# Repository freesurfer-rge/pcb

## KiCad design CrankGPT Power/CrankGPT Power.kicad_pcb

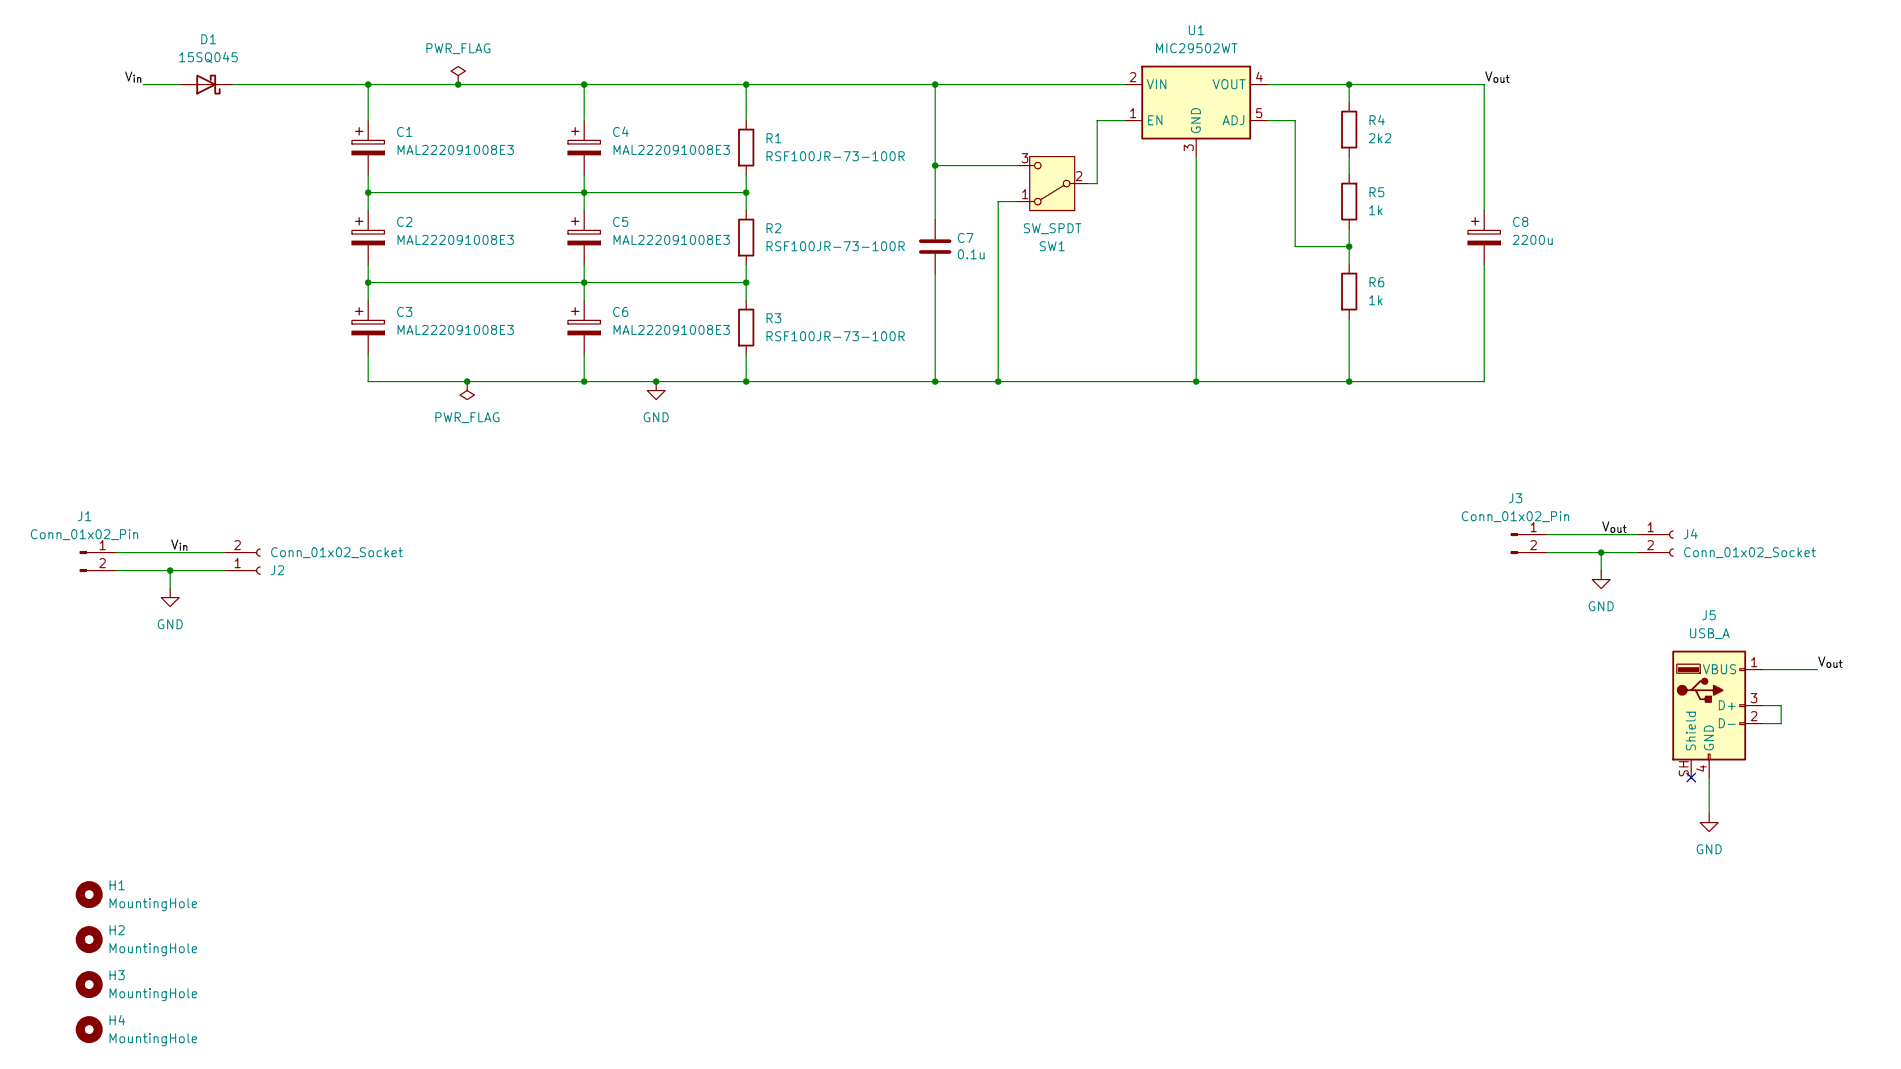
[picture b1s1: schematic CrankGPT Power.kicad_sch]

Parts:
C1, C2, C3, C4, C5, C6: MAL222091008E3; CP_Radial_D18.0mm_P7.50mm
C7: 0.1u; C_Disc_D4.3mm_W1.9mm_P5.00mm
C8: 2200u; CP_Radial_D10.0mm_P5.00mm
D1: 15SQ045; D_P600_R-6_P20.00mm_Horizontal
H1, H2, H3, H4: MountingHole; MountingHole_2.7mm_M2.5
J1, J3: Conn_01x02_Pin; PinHeader_1x02_P2.54mm_Vertical
J2, J4: Conn_01x02_Socket; JST_NV_B02P-NV_1x02_P5.00mm_Vertical
J5: USB_A; USB_A_Molex_67643_Horizontal
R1, R2, R3: RSF100JR-73-100R; R_Axial_DIN0414_L11.9mm_D4.5mm_P15.24mm_Horizontal
R4: 2k2; R_Axial_DIN0207_L6.3mm_D2.5mm_P7.62mm_Horizontal
R5, R6: 1k; R_Axial_DIN0207_L6.3mm_D2.5mm_P7.62mm_Horizontal
SW1: SW_SPDT; SW_Slide_SPDT_Angled_CK_OS102011MA1Q
U1: MIC29502WT; TO-220-5_P3.4x3.7mm_StaggerEven_Lead3.8mm_Vertical

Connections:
/V_{in}: D1.2 (A), J1.1, J2.2
/V_{out}: C8.1, J3.1, J4.1, J5.1 (VBUS), R4.1, U1.4 (VOUT)
GND: C3.2, C6.2, C7.1, C8.2, J1.2, J2.1, J3.2, J4.2, J5.4 (GND), R3.2, R6.2, SW1.1 (A), U1.3 (GND)
unnamed: C1.2, C2.1, C4.2, C5.1, R1.2, R2.1
unnamed: C2.2, C3.1, C5.2, C6.1, R2.2, R3.1
unnamed: C1.1, C4.1, C7.2, D1.1 (K), R1.1, SW1.3 (C), U1.2 (VIN)
unnamed: J5.2 (D-), J5.3 (D+)
unnamed: R4.2, R5.2
unnamed: SW1.2 (B), U1.1 (EN)
unnamed: R5.1, R6.1, U1.5 (ADJ)

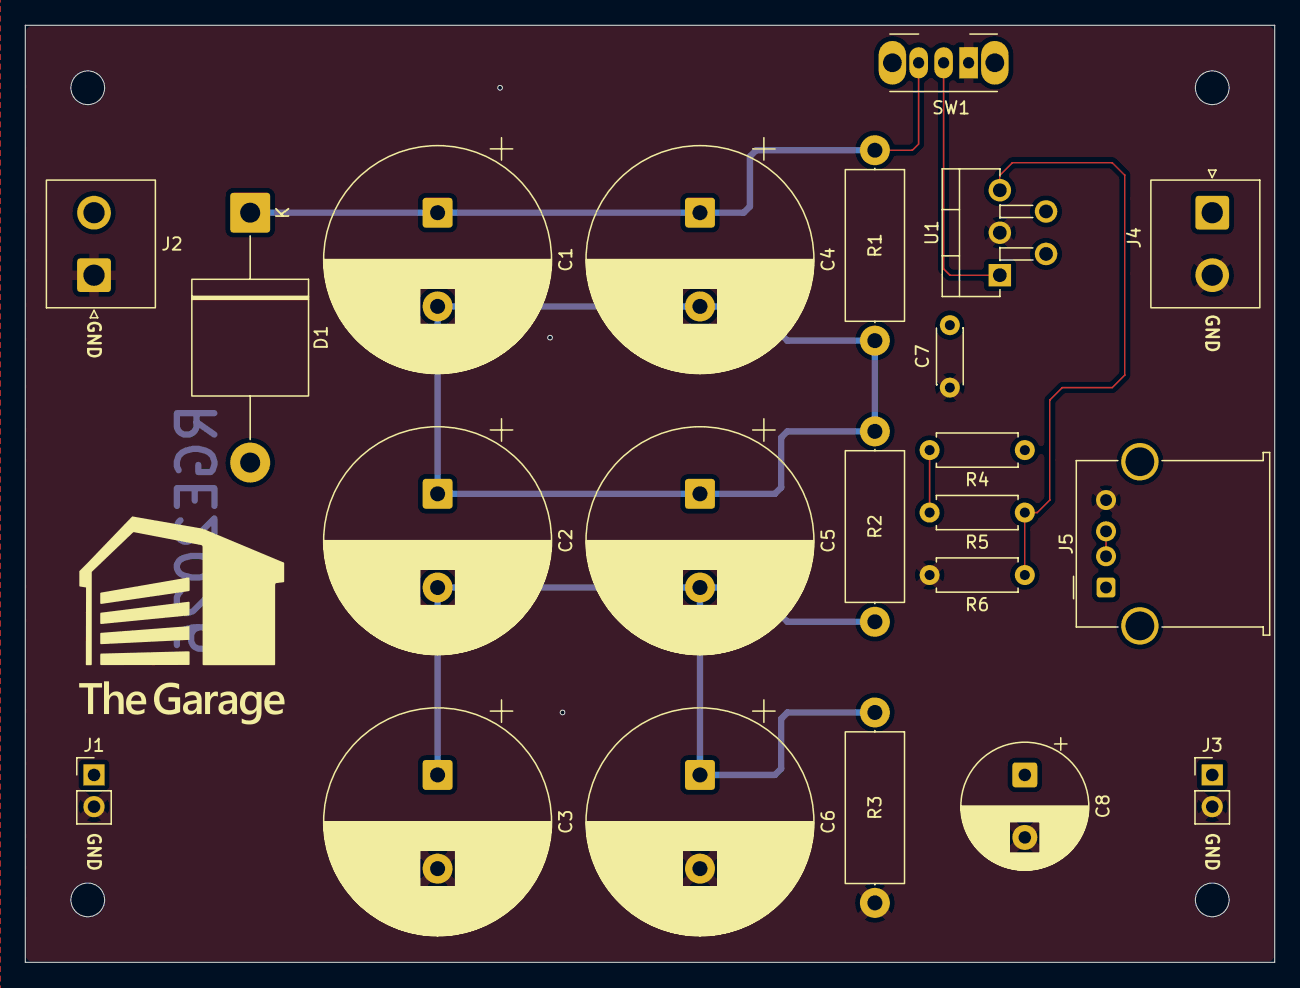
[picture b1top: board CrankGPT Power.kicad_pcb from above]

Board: 2 copper layers, 100.0 x 75.0 mm, 26 parts (0 on the bottom side), 10 nets.

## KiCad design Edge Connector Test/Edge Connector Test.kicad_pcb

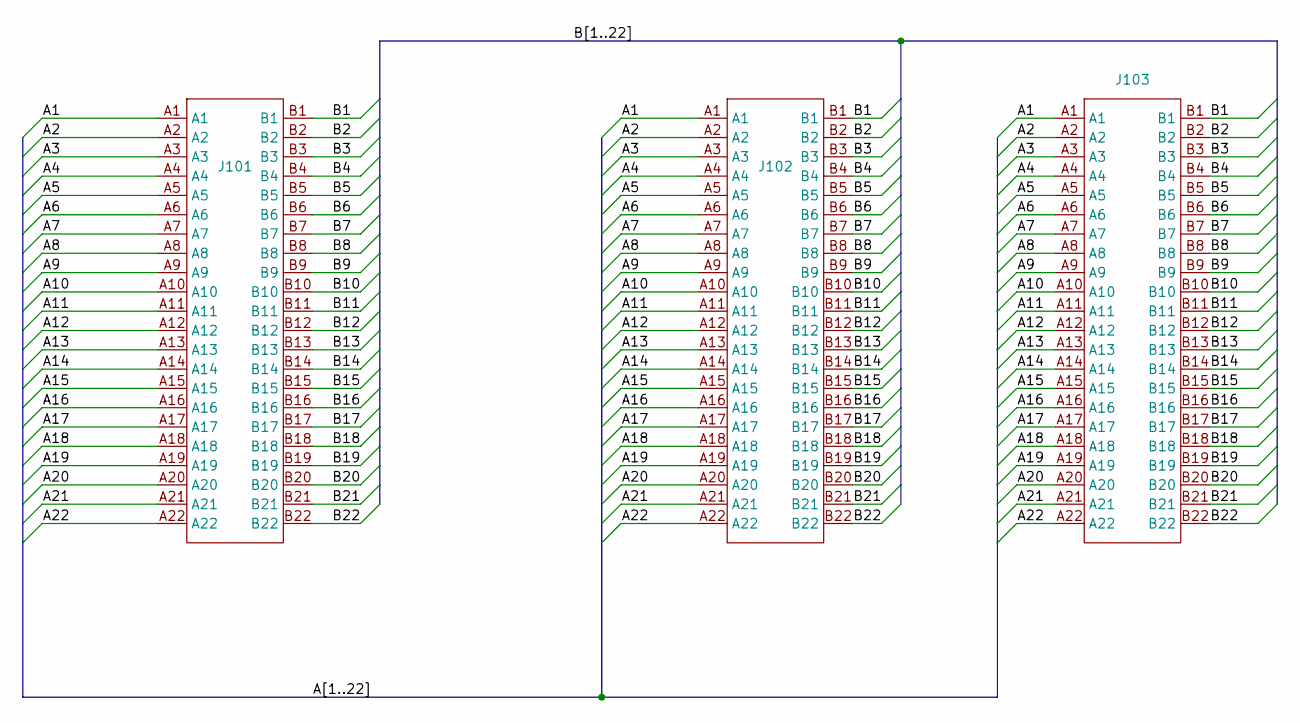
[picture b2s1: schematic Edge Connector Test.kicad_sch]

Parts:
J101, J102: TE-5530843-4-Mount
J103: TE-5530843-4-Edge

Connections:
/A1: J101.A1, J102.A1, J103.A1
/A2: J101.A2, J102.A2, J103.A2
/A3: J101.A3, J102.A3, J103.A3
/A4: J101.A4, J102.A4, J103.A4
/A5: J101.A5, J102.A5, J103.A5
/A6: J101.A6, J102.A6, J103.A6
/A7: J101.A7, J102.A7, J103.A7
/A8: J101.A8, J102.A8, J103.A8
/A9: J101.A9, J102.A9, J103.A9
/A10: J101.A10, J102.A10, J103.A10
/A11: J101.A11, J102.A11, J103.A11
/A12: J101.A12, J102.A12, J103.A12
/A13: J101.A13, J102.A13, J103.A13
/A14: J101.A14, J102.A14, J103.A14
/A15: J101.A15, J102.A15, J103.A15
/A16: J101.A16, J102.A16, J103.A16
/A17: J101.A17, J102.A17, J103.A17
/A18: J101.A18, J102.A18, J103.A18
/A19: J101.A19, J102.A19, J103.A19
/A20: J101.A20, J102.A20, J103.A20
/A21: J101.A21, J102.A21, J103.A21
/A22: J101.A22, J102.A22, J103.A22
/B1: J101.B1, J102.B1, J103.B1
/B2: J101.B2, J102.B2, J103.B2
/B3: J101.B3, J102.B3, J103.B3
/B4: J101.B4, J102.B4, J103.B4
/B5: J101.B5, J102.B5, J103.B5
/B6: J101.B6, J102.B6, J103.B6
/B7: J101.B7, J102.B7, J103.B7
/B8: J101.B8, J102.B8, J103.B8
/B9: J101.B9, J102.B9, J103.B9
/B10: J101.B10, J102.B10, J103.B10
/B11: J101.B11, J102.B11, J103.B11
/B12: J101.B12, J102.B12, J103.B12
/B13: J101.B13, J102.B13, J103.B13
/B14: J101.B14, J102.B14, J103.B14
/B15: J101.B15, J102.B15, J103.B15
/B16: J101.B16, J102.B16, J103.B16
/B17: J101.B17, J102.B17, J103.B17
/B18: J101.B18, J102.B18, J103.B18
/B19: J101.B19, J102.B19, J103.B19
/B20: J101.B20, J102.B20, J103.B20
/B21: J101.B21, J102.B21, J103.B21
/B22: J101.B22, J102.B22, J103.B22

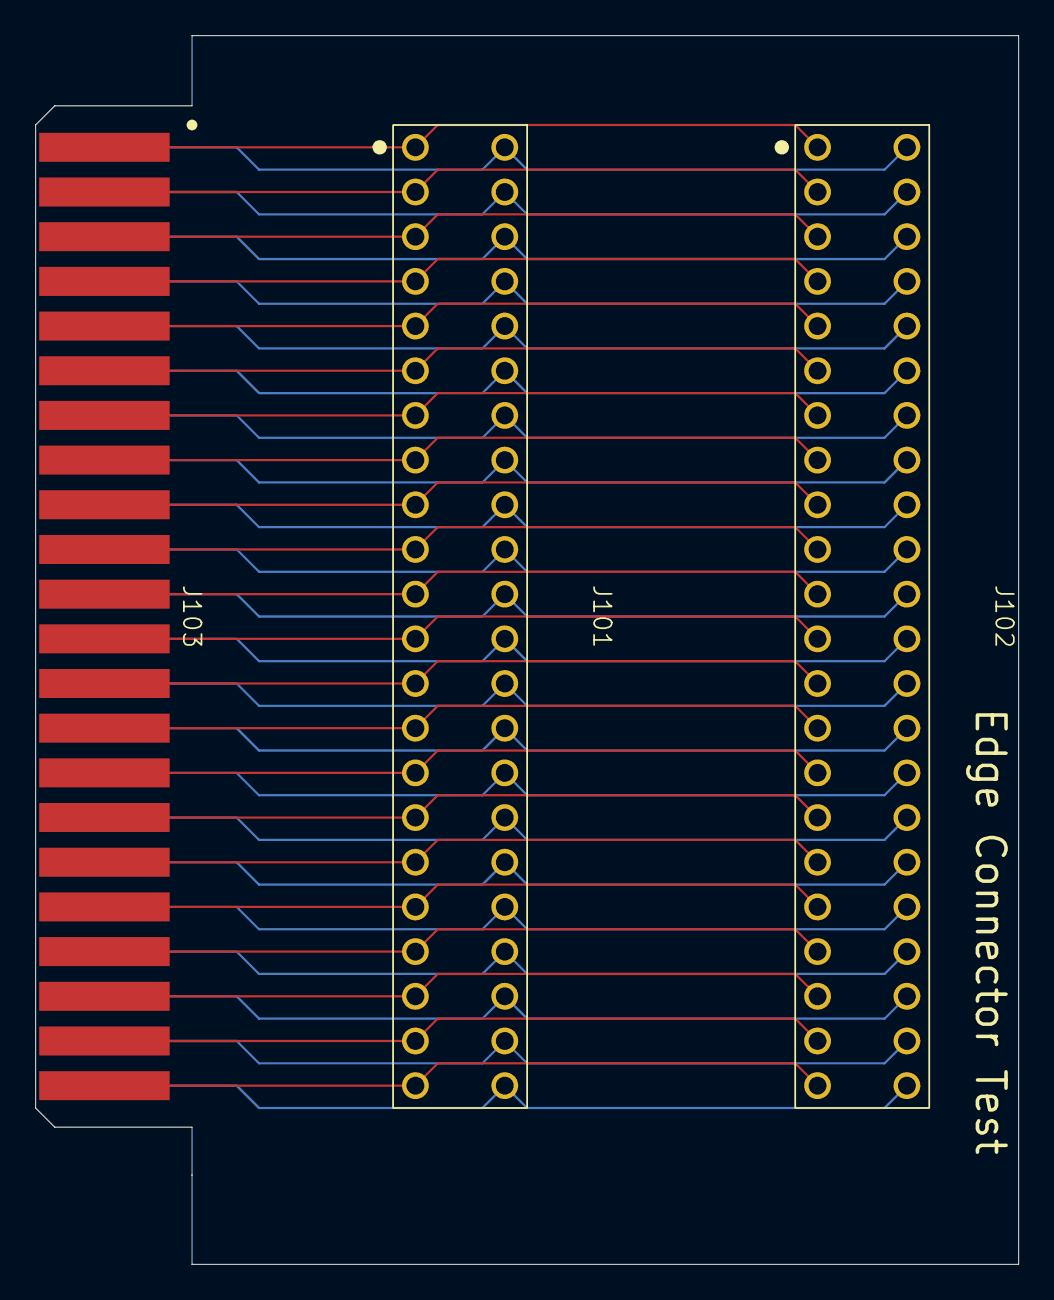
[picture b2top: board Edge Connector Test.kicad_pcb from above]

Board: 2 copper layers, 55.9 x 69.8 mm, 3 parts (0 on the bottom side), 44 nets.

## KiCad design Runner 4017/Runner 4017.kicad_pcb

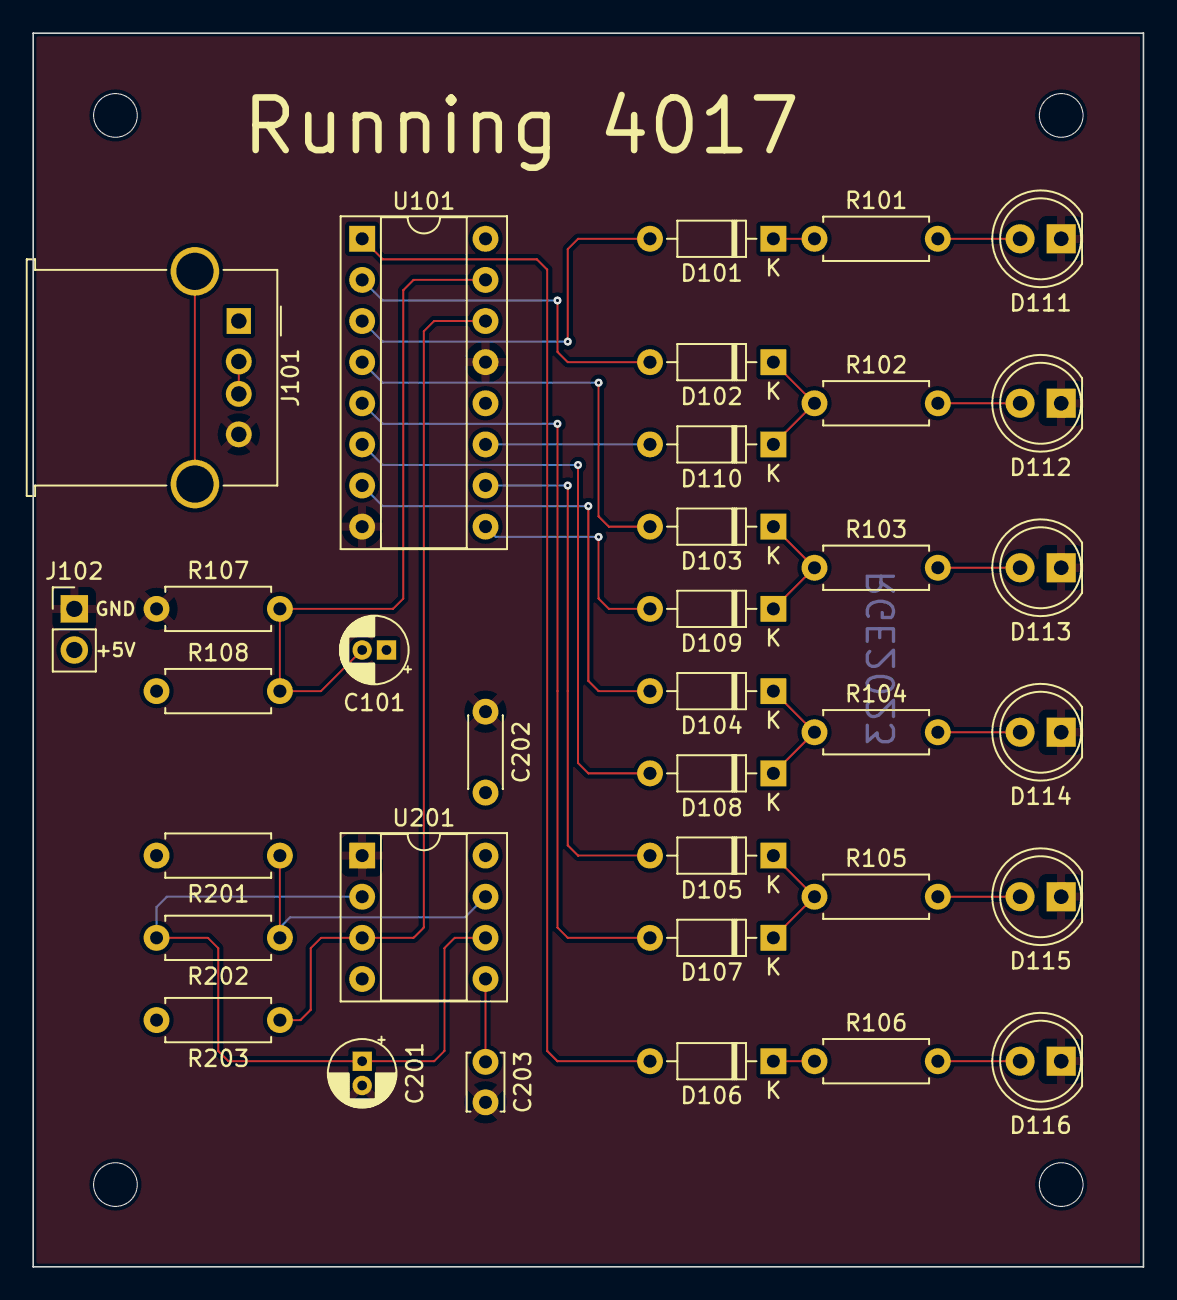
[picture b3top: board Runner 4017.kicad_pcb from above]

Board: 2 copper layers, 68.6 x 76.2 mm, 39 parts (0 on the bottom side), 30 nets.

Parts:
C101, C201: 10u; CP_Radial_D4.0mm_P1.50mm
C202: 0.1u; C_Disc_D4.3mm_W1.9mm_P5.00mm
C203: 0.01u; C_Disc_D3.4mm_W2.1mm_P2.50mm
D101, D102, D103, D104, D105, D106, D107, D108, D109, D110: 1N4148; D_DO-35_SOD27_P7.62mm_Horizontal
D111, D112, D113, D114, D115, D116: LED; LED_D5.0mm
H101, H102, H103, H104: MountingHole; MountingHole_2.7mm_M2.5_ISO7380
J101: USB_A; USB_A_Molex_67643_Horizontal
J102: Conn_01x02_Pin; PinHeader_1x02_P2.54mm_Vertical
R101, R102, R103, R104, R105, R106: R; R_Axial_DIN0207_L6.3mm_D2.5mm_P7.62mm_Horizontal
R107, R203: 1k; R_Axial_DIN0207_L6.3mm_D2.5mm_P7.62mm_Horizontal
R108: 100k; R_Axial_DIN0207_L6.3mm_D2.5mm_P7.62mm_Horizontal
R201: 10k; R_Axial_DIN0207_L6.3mm_D2.5mm_P7.62mm_Horizontal
R202: 22k; R_Axial_DIN0207_L6.3mm_D2.5mm_P7.62mm_Horizontal
U101: 4017; DIP-16_W7.62mm_Socket
U201: LM555xN; DIP-8_W7.62mm_Socket

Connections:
+5V: C101.1, C202.2, J101.1 (VBUS), J102.2, R108.1, R201.2, R203.2, U101.16 (VDD), U201.4 (R), U201.8 (VCC)
/Clock/CLK: R203.1, U101.14 (CLK), U201.3 (Q)
/Clock/DIVIDER: R201.1, R202.1, U201.7 (DIS)
/Clock/TRTHR: C201.1, R202.2, U201.2 (TR), U201.6 (THR)
/LED1: D101.1 (K), R101.1
/LED2: D102.1 (K), D110.1 (K), R102.1
/LED3: D103.1 (K), D109.1 (K), R103.1
/LED4: D104.1 (K), D108.1 (K), R104.1
/LED5: D105.1 (K), D107.1 (K), R105.1
/LED6: D106.1 (K), R106.1
/RESET: C101.2, R107.2, R108.2, U101.15 (Reset)
GND: C201.2, C202.1, C203.2, D111.1 (K), D112.1 (K), D113.1 (K), D114.1 (K), D115.1 (K), D116.1 (K), J101.4 (GND), J102.1, R107.1, U101.8 (VSS), U101.13 (CKEN), U201.1 (GND)
unnamed: D101.2 (A), U101.3 (Q0)
unnamed: D102.2 (A), U101.2 (Q1)
unnamed: D103.2 (A), U101.4 (Q2)
unnamed: D104.2 (A), U101.7 (Q3)
unnamed: D105.2 (A), U101.10 (Q4)
unnamed: D106.2 (A), U101.1 (Q5)
unnamed: D107.2 (A), U101.5 (Q6)
unnamed: D108.2 (A), U101.6 (Q7)
unnamed: D109.2 (A), U101.9 (Q8)
unnamed: D110.2 (A), U101.11 (Q9)
unnamed: D111.2 (A), R101.2
unnamed: D112.2 (A), R102.2
unnamed: D113.2 (A), R103.2
unnamed: D114.2 (A), R104.2
unnamed: D115.2 (A), R105.2
unnamed: D116.2 (A), R106.2
unnamed: J101.2 (D-), J101.3 (D+)
unnamed: C203.1, U201.5 (CV)

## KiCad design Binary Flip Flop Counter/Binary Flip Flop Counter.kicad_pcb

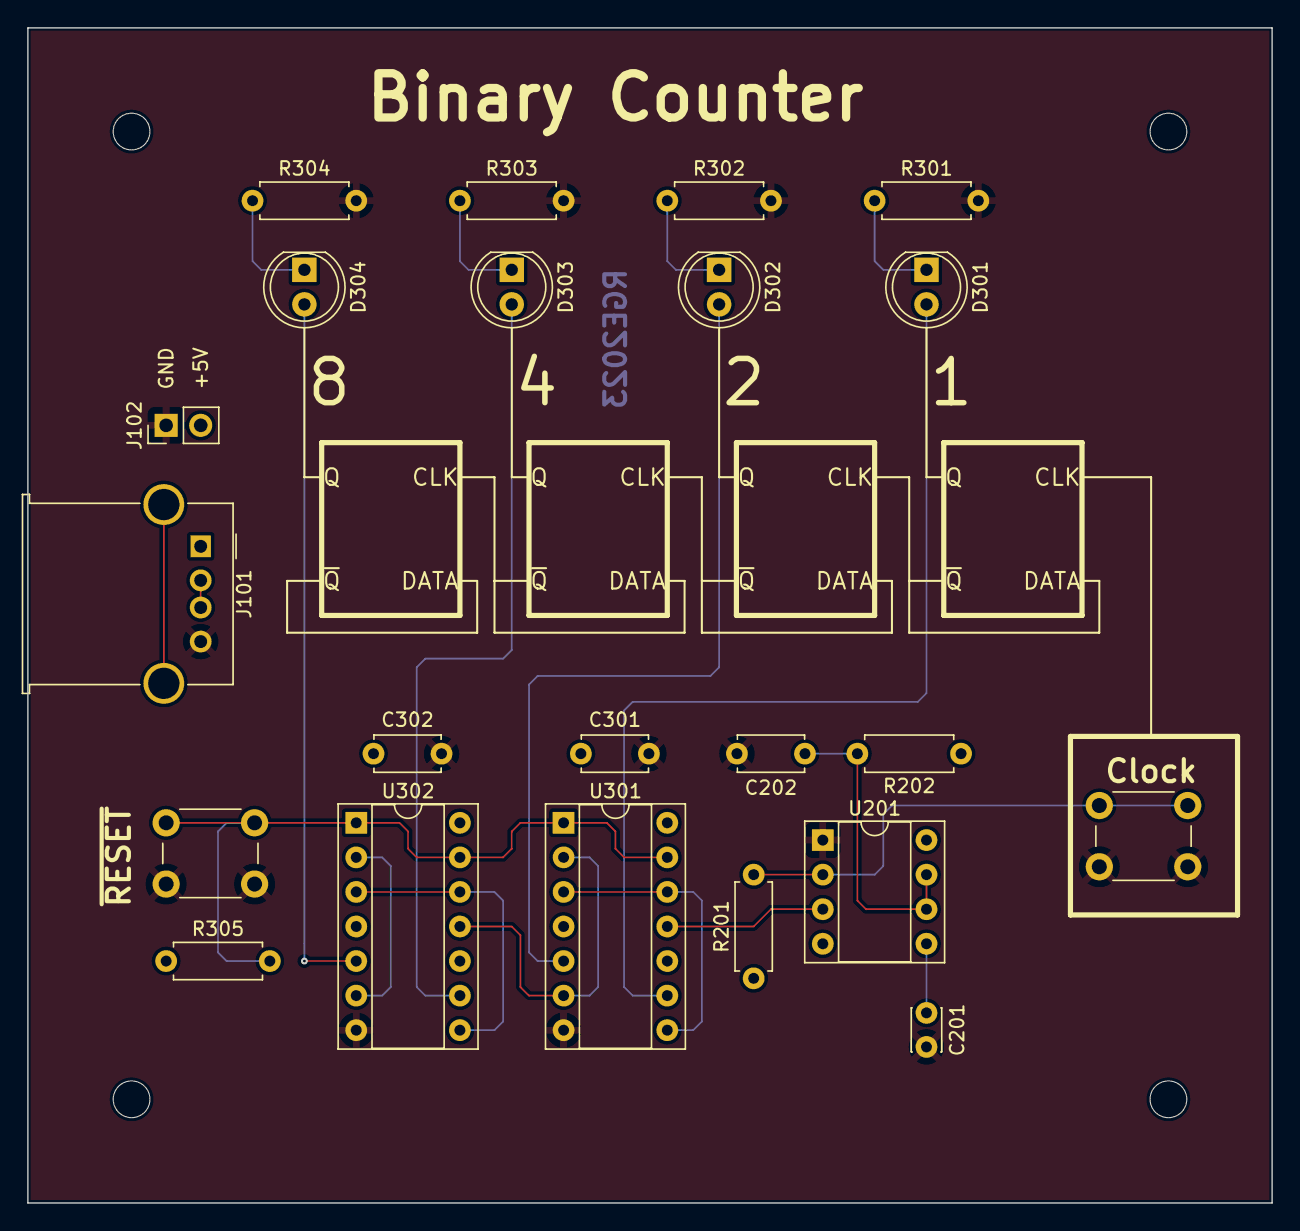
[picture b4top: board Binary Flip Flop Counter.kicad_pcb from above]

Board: 2 copper layers, 91.4 x 86.4 mm, 26 parts (0 on the bottom side), 20 nets.

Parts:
C201: 10nF; C_Disc_D3.0mm_W2.0mm_P2.50mm
C202, C301, C302: 0.1u; C_Disc_D4.7mm_W2.5mm_P5.00mm
D301, D302, D303, D304: LED; LED_D5.0mm
H101, H102, H103, H104: MountingHole; MountingHole_2.7mm_M2.5_ISO7380
J101: USB_A; USB_A_Molex_67643_Horizontal
J102: Conn_01x02_Pin; PinHeader_1x02_P2.54mm_Vertical
R201: 22k; R_Axial_DIN0207_L6.3mm_D2.5mm_P7.62mm_Horizontal
R202: 1M; R_Axial_DIN0207_L6.3mm_D2.5mm_P7.62mm_Horizontal
R301, R302, R303, R304: 4k7; R_Axial_DIN0207_L6.3mm_D2.5mm_P7.62mm_Horizontal
R305: 100k; R_Axial_DIN0207_L6.3mm_D2.5mm_P7.62mm_Horizontal
SW201, SW301: SW_Push; SW_PUSH_6mm_H4.3mm
U201: LM555xM; DIP-8_W7.62mm_Socket
U301, U302: 74HC74; DIP-14_W7.62mm_Socket

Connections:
+5V: C301.1, C302.1, J101.1 (VBUS), J102.2, R201.1, R202.1, R305.1, U201.4 (R), U201.8 (VCC), U301.4 (~S), U301.10 (~S), U301.14 (VCC), U302.4 (~S), U302.10 (~S), U302.14 (VCC)
/Counter/CLK: U201.3 (Q), U301.11 (C)
/Counter/Out0: D301.2 (A), U301.9 (Q)
/Counter/Out1: D302.2 (A), U301.5 (Q)
/Counter/Out2: D303.2 (A), U302.9 (Q)
/Counter/Out3: D304.2 (A), U302.5 (Q)
/Counter/~Q_{0}: U301.3 (C), U301.8 (~Q), U301.12 (D)
/Counter/~Q_{1}: U301.2 (D), U301.6 (~Q), U302.11 (C)
/Counter/~Q_{2}: U302.3 (C), U302.8 (~Q), U302.12 (D)
/Counter/~Q_{3}: U302.2 (D), U302.6 (~Q)
/Counter/~RESET: R305.2, SW301.1, U301.1 (~R), U301.13 (~R), U302.1 (~R), U302.13 (~R)
GND: C201.2, C202.2, C301.2, C302.2, J101.4 (GND), J102.1, R301.2, R302.2, R303.2, R304.2, SW201.2, SW301.2, U201.1 (GND), U301.7 (GND), U302.7 (GND)
unnamed: D301.1 (K), R301.1
unnamed: D302.1 (K), R302.1
unnamed: D303.1 (K), R303.1
unnamed: D304.1 (K), R304.1
unnamed: J101.2 (D-), J101.3 (D+)
unnamed: C201.1, U201.5 (CV)
unnamed: C202.1, R202.2, U201.6 (THR), U201.7 (DIS)
unnamed: R201.2, SW201.1, U201.2 (TR)

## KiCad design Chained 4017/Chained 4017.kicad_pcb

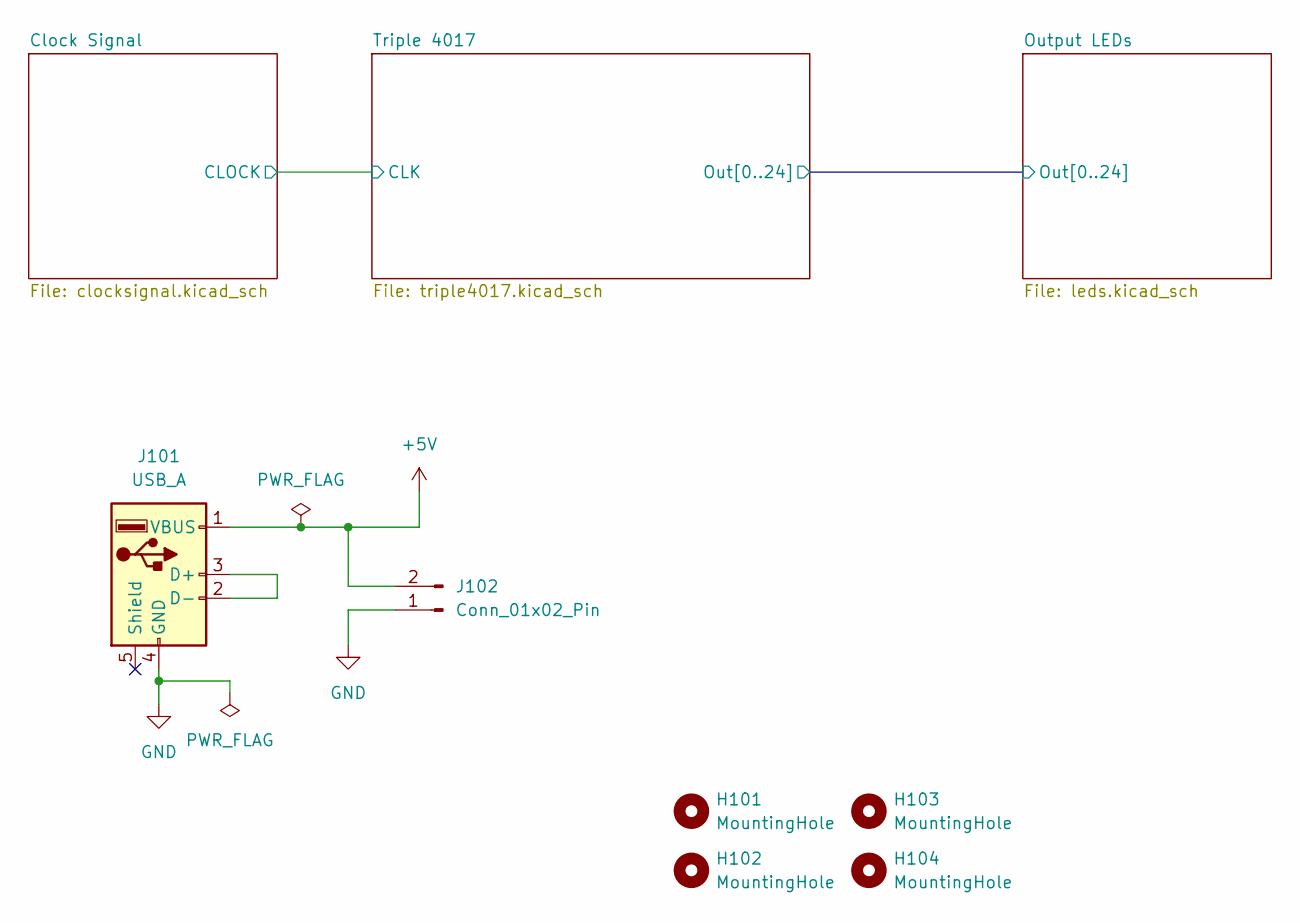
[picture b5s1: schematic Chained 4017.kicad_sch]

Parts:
H101, H102, H103, H104: MountingHole; MountingHole_2.7mm_M2.5_ISO7380
J101: USB_A; USB_A_Molex_67643_Horizontal
J102: Conn_01x02_Pin; PinHeader_1x02_P2.54mm_Vertical

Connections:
unnamed: J101.2 (D-), J101.3 (D+)

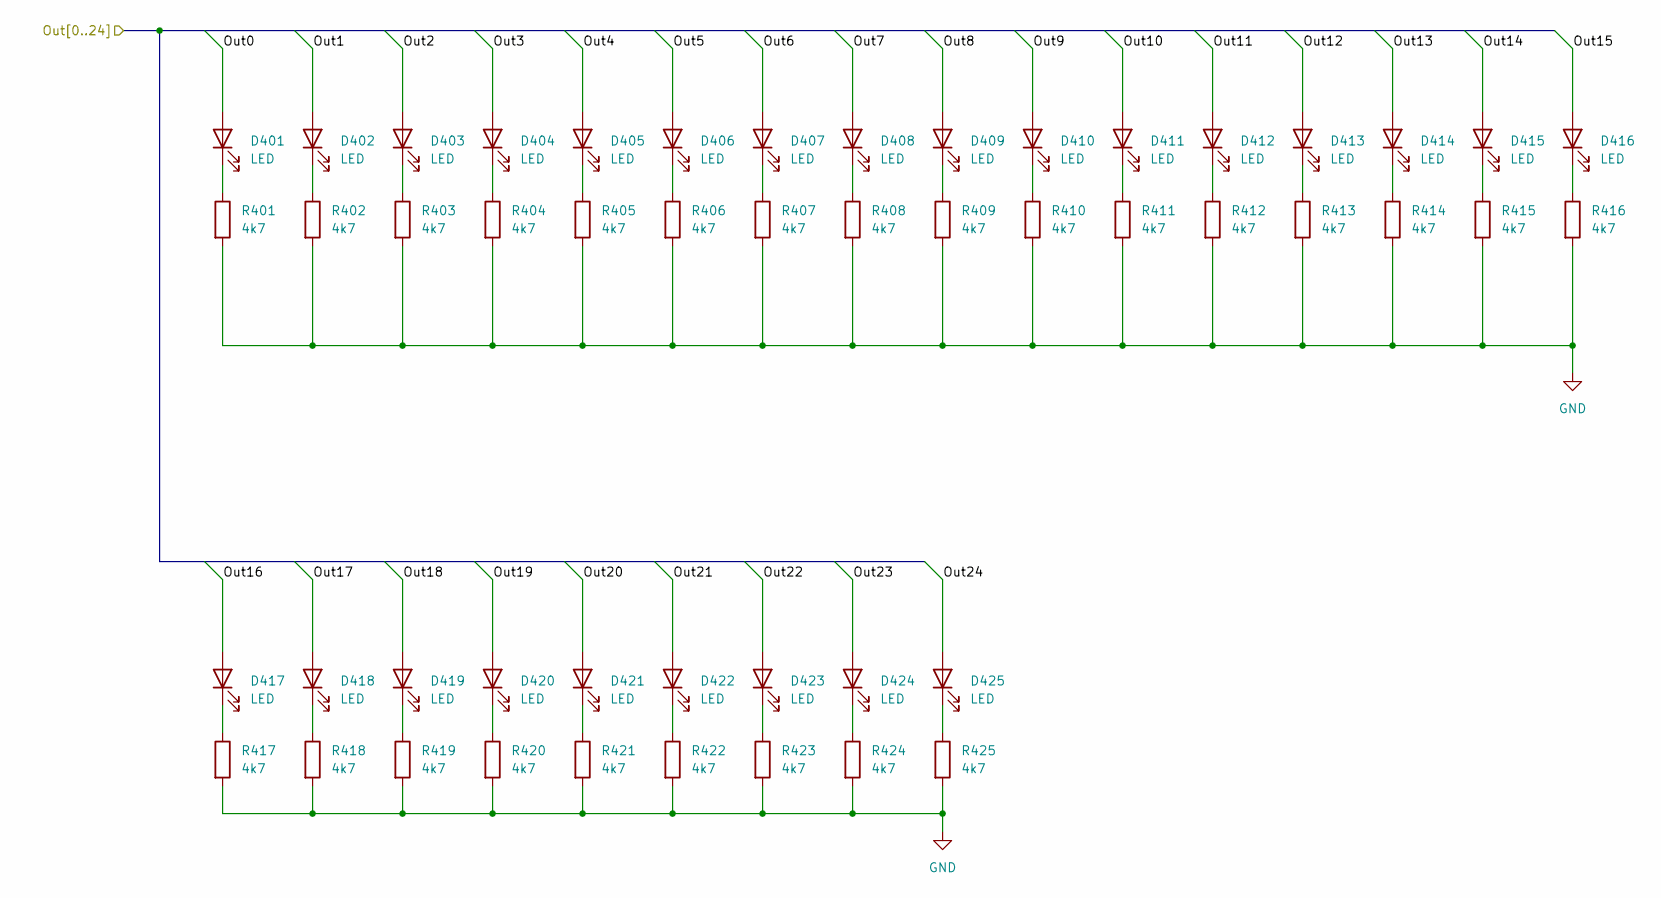
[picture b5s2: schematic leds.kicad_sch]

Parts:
D401, D402, D403, D404, D405, D406, D407, D408, D409, D410, D411, D412, D413, D414, D415, D416, D417, D418, D419, D420, D421, D422, D423, D424, D425: LED; LED_D5.0mm
R401, R402, R403, R404, R405, R406, R407, R408, R409, R410, R411, R412, R413, R414, R415, R416, R417, R418, R419, R420, R421, R422, R423, R424, R425: 4k7; R_Axial_DIN0207_L6.3mm_D2.5mm_P7.62mm_Horizontal

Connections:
/Output LEDs/Out0: D401.2 (A); also elsewhere on the board
/Output LEDs/Out1: D402.2 (A); also elsewhere on the board
/Output LEDs/Out2: D403.2 (A); also elsewhere on the board
/Output LEDs/Out3: D404.2 (A); also elsewhere on the board
/Output LEDs/Out4: D405.2 (A); also elsewhere on the board
/Output LEDs/Out5: D406.2 (A); also elsewhere on the board
/Output LEDs/Out6: D407.2 (A); also elsewhere on the board
/Output LEDs/Out7: D408.2 (A); also elsewhere on the board
/Output LEDs/Out8: D409.2 (A); also elsewhere on the board
/Output LEDs/Out9: D410.2 (A); also elsewhere on the board
/Output LEDs/Out10: D411.2 (A); also elsewhere on the board
/Output LEDs/Out11: D412.2 (A); also elsewhere on the board
/Output LEDs/Out12: D413.2 (A); also elsewhere on the board
/Output LEDs/Out13: D414.2 (A); also elsewhere on the board
/Output LEDs/Out14: D415.2 (A); also elsewhere on the board
/Output LEDs/Out15: D416.2 (A); also elsewhere on the board
/Output LEDs/Out16: D417.2 (A); also elsewhere on the board
/Output LEDs/Out17: D418.2 (A); also elsewhere on the board
/Output LEDs/Out18: D419.2 (A); also elsewhere on the board
/Output LEDs/Out19: D420.2 (A); also elsewhere on the board
/Output LEDs/Out20: D421.2 (A); also elsewhere on the board
/Output LEDs/Out21: D422.2 (A); also elsewhere on the board
/Output LEDs/Out22: D423.2 (A); also elsewhere on the board
/Output LEDs/Out23: D424.2 (A); also elsewhere on the board
/Output LEDs/Out24: D425.2 (A); also elsewhere on the board
unnamed: D401.1 (K), R401.1
unnamed: D402.1 (K), R402.1
unnamed: D403.1 (K), R403.1
unnamed: D404.1 (K), R404.1
unnamed: D405.1 (K), R405.1
unnamed: D406.1 (K), R406.1
unnamed: D407.1 (K), R407.1
unnamed: D408.1 (K), R408.1
unnamed: D409.1 (K), R409.1
unnamed: D410.1 (K), R410.1
unnamed: D411.1 (K), R411.1
unnamed: D412.1 (K), R412.1
unnamed: D413.1 (K), R413.1
unnamed: D414.1 (K), R414.1
unnamed: D415.1 (K), R415.1
unnamed: D416.1 (K), R416.1
unnamed: D417.1 (K), R417.1
unnamed: D418.1 (K), R418.1
unnamed: D419.1 (K), R419.1
unnamed: D420.1 (K), R420.1
unnamed: D421.1 (K), R421.1
unnamed: D422.1 (K), R422.1
unnamed: D423.1 (K), R423.1
unnamed: D424.1 (K), R424.1
unnamed: D425.1 (K), R425.1

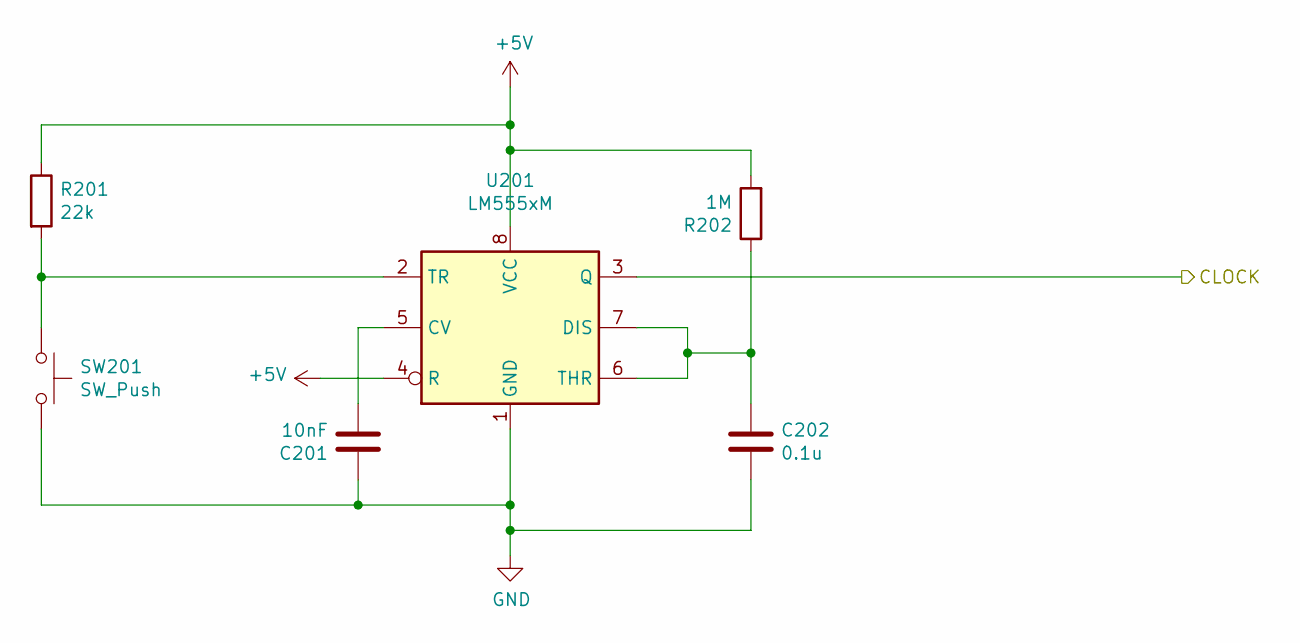
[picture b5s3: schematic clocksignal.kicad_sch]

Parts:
C201: 10nF; C_Disc_D3.0mm_W2.0mm_P2.50mm
C202: 0.1u; C_Disc_D4.7mm_W2.5mm_P5.00mm
R201: 22k; R_Axial_DIN0207_L6.3mm_D2.5mm_P7.62mm_Horizontal
R202: 1M; R_Axial_DIN0207_L6.3mm_D2.5mm_P7.62mm_Horizontal
SW201: SW_Push; SW_PUSH_6mm_H4.3mm
U201: LM555xM; DIP-8_W7.62mm_Socket

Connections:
/Clock Signal/CLOCK: U201.3 (Q); also elsewhere on the board
unnamed: R201.2, SW201.1, U201.2 (TR)

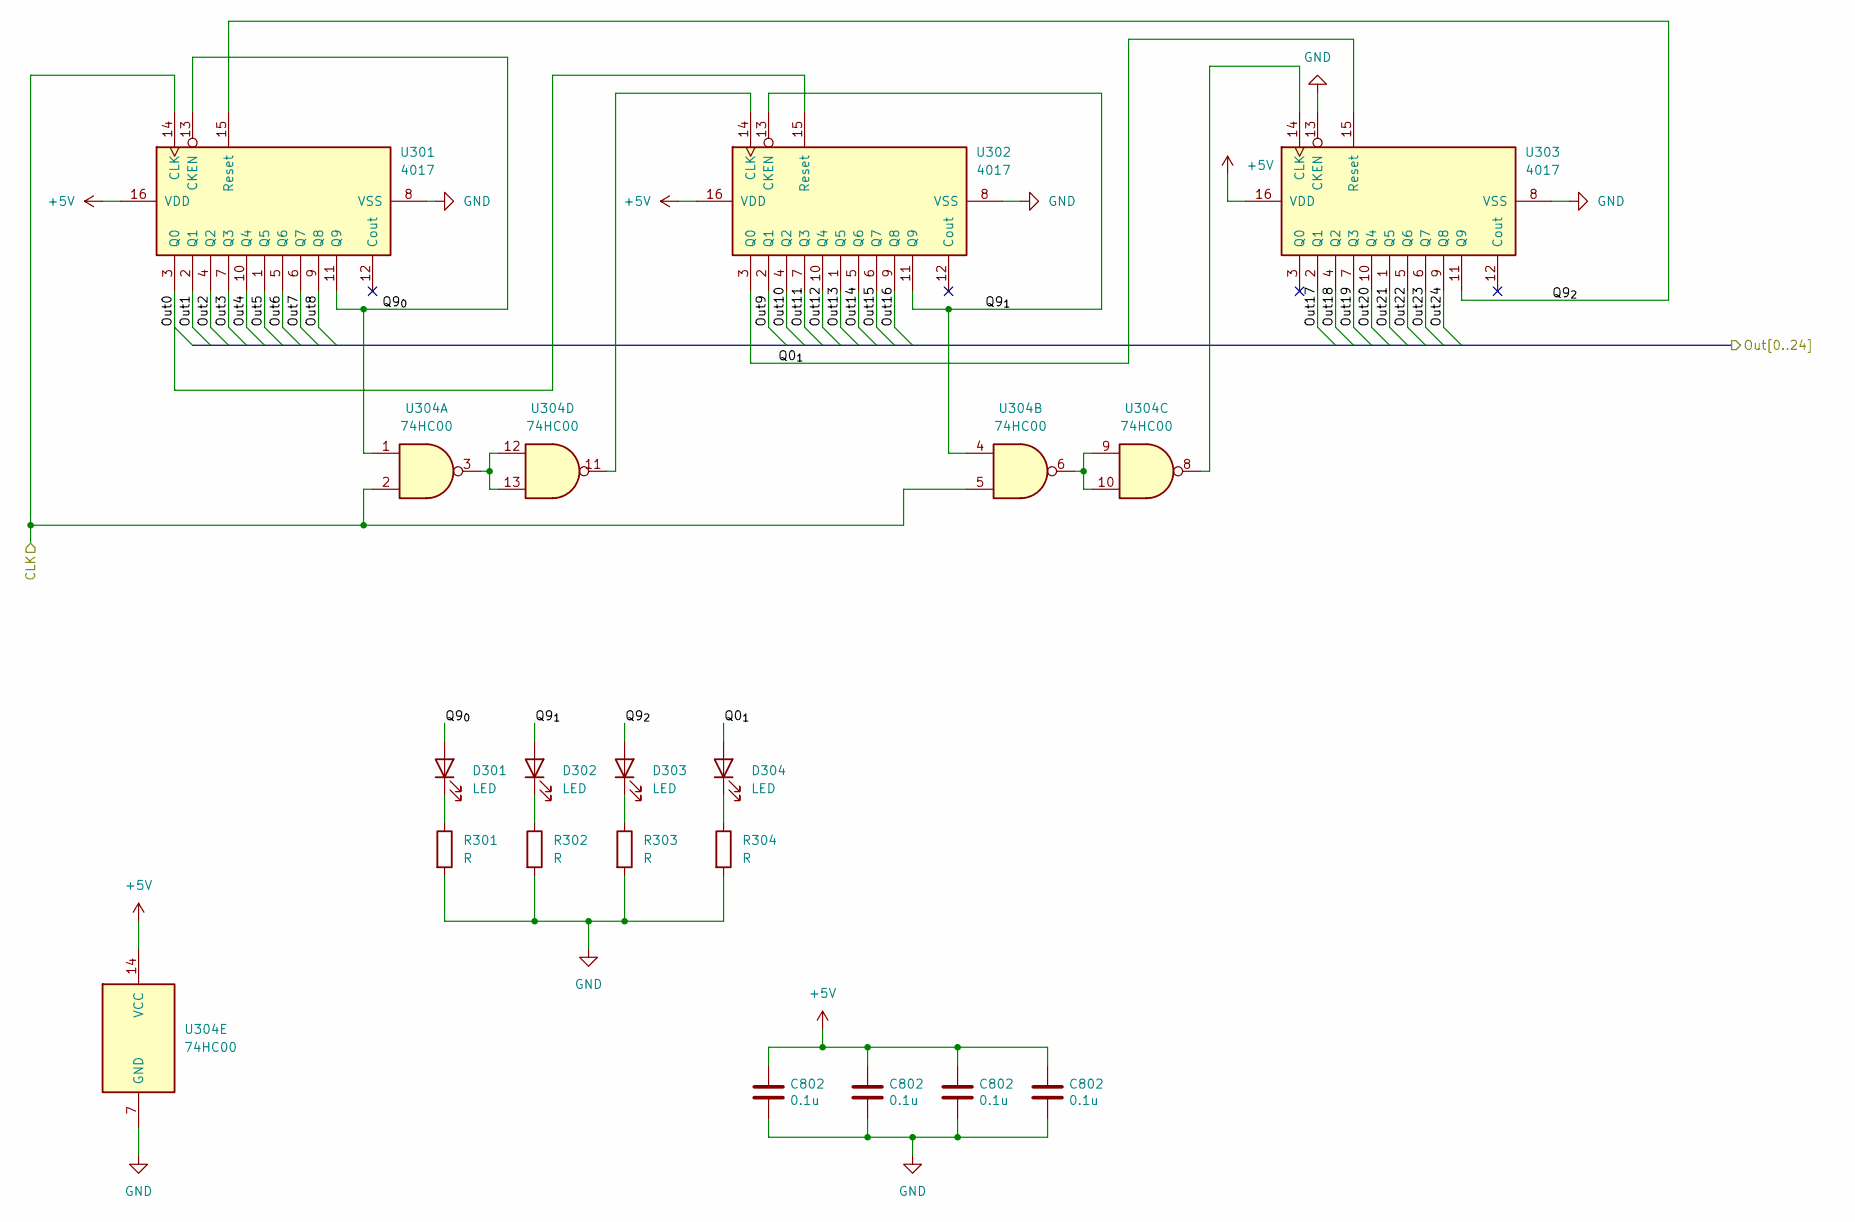
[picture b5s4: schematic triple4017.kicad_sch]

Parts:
C802: 0.1u; C_Disc_D4.3mm_W1.9mm_P5.00mm
D301, D302, D303, D304: LED; LED_D3.0mm
R301, R302, R303, R304: R; R_Axial_DIN0207_L6.3mm_D2.5mm_P7.62mm_Horizontal
U301, U302, U303: 4017; DIP-16_W7.62mm_Socket
U304: 74HC00; DIP-14_W7.62mm_Socket

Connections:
/Clock Signal/CLOCK: U301.14 (CLK), U304.2, U304.5; also elsewhere on the board
/Output LEDs/Out0: U301.3 (Q0), U302.15 (Reset); also elsewhere on the board
/Output LEDs/Out1: U301.2 (Q1); also elsewhere on the board
/Output LEDs/Out2: U301.4 (Q2); also elsewhere on the board
/Output LEDs/Out3: U301.7 (Q3); also elsewhere on the board
/Output LEDs/Out4: U301.10 (Q4); also elsewhere on the board
/Output LEDs/Out5: U301.1 (Q5); also elsewhere on the board
/Output LEDs/Out6: U301.5 (Q6); also elsewhere on the board
/Output LEDs/Out7: U301.6 (Q7); also elsewhere on the board
/Output LEDs/Out8: U301.9 (Q8); also elsewhere on the board
/Output LEDs/Out9: U302.2 (Q1); also elsewhere on the board
/Output LEDs/Out10: U302.4 (Q2); also elsewhere on the board
/Output LEDs/Out11: U302.7 (Q3); also elsewhere on the board
/Output LEDs/Out12: U302.10 (Q4); also elsewhere on the board
/Output LEDs/Out13: U302.1 (Q5); also elsewhere on the board
/Output LEDs/Out14: U302.5 (Q6); also elsewhere on the board
/Output LEDs/Out15: U302.6 (Q7); also elsewhere on the board
/Output LEDs/Out16: U302.9 (Q8); also elsewhere on the board
/Output LEDs/Out17: U303.2 (Q1); also elsewhere on the board
/Output LEDs/Out18: U303.4 (Q2); also elsewhere on the board
/Output LEDs/Out19: U303.7 (Q3); also elsewhere on the board
/Output LEDs/Out20: U303.10 (Q4); also elsewhere on the board
/Output LEDs/Out21: U303.1 (Q5); also elsewhere on the board
/Output LEDs/Out22: U303.5 (Q6); also elsewhere on the board
/Output LEDs/Out23: U303.6 (Q7); also elsewhere on the board
/Output LEDs/Out24: U303.9 (Q8); also elsewhere on the board
/Triple 4017/Q0_{1}: D304.2 (A), U302.3 (Q0), U303.15 (Reset)
/Triple 4017/Q9_{0}: D301.2 (A), U301.11 (Q9), U301.13 (CKEN), U304.1
/Triple 4017/Q9_{1}: D302.2 (A), U302.11 (Q9), U302.13 (CKEN), U304.4
/Triple 4017/Q9_{2}: D303.2 (A), U301.15 (Reset), U303.11 (Q9)
unnamed: D301.1 (K), R301.1
unnamed: D302.1 (K), R302.1
unnamed: D303.1 (K), R303.1
unnamed: D304.1 (K), R304.1
unnamed: U302.14 (CLK), U304.11
unnamed: U303.14 (CLK), U304.8
unnamed: U304.6, U304.9, U304.10
unnamed: U304.3, U304.12, U304.13

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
